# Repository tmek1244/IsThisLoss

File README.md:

# In progress
---

# Split keyboard IsThisLoss 

Welcome to the IsThisLoss repository. In this README you will find my knowledge about split keyboards, usefull materials to learn from, my steps of building this keyboard, tools I used etc. Hope that will help someone, same as mamy other usefull sources helped me.

## Table of Contents

- [Project Overview](#project-overview)
- [Usefull Recourses and Tools](#usefull-resources-and-tools)
- [Keyboard Design](#keyboard-design)
- [Tips & Tricks](#tips--tricks)

---

## Project Overview

This project is a documentation of my journey in creating a custom split keyboard. It encompasses every stage of the process, from the initial design concept to the final product. Whether you're a fellow keyboard enthusiast or just curious about the DIY keyboard-making world, this repository is meant to inspire, educate, and entertain.

## Usefull Recourses and Tools

### Youtube videos
Here are three great videos from [Ben Vallack](https://www.youtube.com/@BenVallack/videos):
- About [Ferris Sweep Compact](https://www.youtube.com/watch?v=JqpBKuEVinw&ab_channel=BenVallack) - process of ordering, customising and building that keyboard
- [Designing your custom keyboard](https://www.youtube.com/watch?v=UKfeJrRIcxw&ab_channel=BenVallack)
- [Designing your custom keyboard in depth](https://www.youtube.com/watch?v=M_VuXVErD6E&ab_channel=BenVallack)
Here is a video about KiCad, rather long tho (1:40) and its probably not necessary, but in case your would like to learn more about this powerfull tool
- [Designing STM32 PCB](https://www.youtube.com/watch?v=aVUqaB0IMh4&ab_channel=Phil%E2%80%99sLab) - KiCad tutorial

### Articles
- [FlatFootFox](https://flatfootfox.com/) - you can find there 6 articles about designing your custom keyboard with Ergogen v4. It starts from [introduction](https://flatfootfox.com/ergogen-introduction/). 
- [Kyria rev3](https://docs.splitkb.com/hc/en-us/sections/6269738440220-Aurora-Kyria-rev3-Build-Guide) - build guide, I was able to better understand building process by reading this article
- [How key matrices works](https://pcbheaven.com/wikipages/How_Key_Matrices_Works/)

### Ergopad
[Tool](https://pashutk.com/ergopad/) allowing you to try and see how your fingers moves and which layout would be the most suitable for you. Quite interesting tool, but after all I haven't used it.

### Ergogen
Open source project on [github](https://github.com/ergogen/ergogen). It provides a common configuration format to describe 2D layout and generate plates, cases and un-routed PCBs. You can clone this repo (which will be usefull at some point) or play with online version. 
There are two available versions [ergogen.xyz](https://ergogen.xyz/) and [ergogen.cache.works](https://ergogen.cache.works/), but I recommend the latter as it shows in real time how would your keyboard looks like. 

### KiCad
KiCad is a free software suite for electronic design automation. It facilitates the design and simulation of electronic hardware. It features an integrated environment for schematic capture, PCB layout, manufacturing file viewing, ngspice-provided SPICE simulation, and engineering calculation.
I found this tool pretty intuitive and if you want to just desing keyboard you really don't need to know much about this software (Ergogen will genereate most of that for you).

### ZMK
[ZMK](https://zmk.dev/) is open source keyboard firmware focused on wireless and battery-powered keyboards. Other popular option for a firmware is [QMK](https://qmk.fm/) but it doesn't support wireless keyboards. Because I wanted to have cleaner setup I went with the former.
You can find my config z[here](https://github.com/tmek1244/zmk-config).

## Keyboard Design
### Intro
I knew which layout looks the best for me - [Kyria rev3](https://splitkb.com/collections/keyboard-kits/products/kyria-rev3-pcb-kit). It has 50 keys which is a lot compared to many other split keyboards ([one key keyboard](https://www.youtube.com/watch?v=vr8LkjsRqZs&ab_channel=BenVallack)), but I didn't want to make it too compact.

### Start with Erogopad
Go checkout [Ergopad](https://pashutk.com/ergopad/), it didn't work for me, but might work for you. Having a tablet would be an advantageous as you will be tapping on screen.

### Create design in Ergogen
I had a lot of struggles with writing anything in Ergogen, until I found a tutorial about new at that time version 4 from FlatFootFox. I encourage you to go check that out. 
Important thing to metion, I only desinged one side (and probably you should too) because get the other one for free! You just put this piece on the other side. This has its consequences, namely the pins on the other side will be reversed. That means that you would have to put microcontroller on the other side too. I didn't like that much so I use footprint suggested by Ben Vallack in one of his tutorials - [promicro pretty](/ergogen/src/footprints/promicro_pretty.js). 
The config is written in yaml, if you're using [ergogen.cache.works](https://ergogen.cache.works/) you can see your progress in real time, which is realy cool. Using Ergogen you can create pcb layout (which is the main advantage), but other staff like creating cases or plates are also great.

After I though I have a good desing I generated `kicad_pcb` file (by clicking Generate on website or running `ergogen input.yaml -o output_folder` in CLI - you have pcb block in your config - [read more](https://docs.ergogen.xyz/pcbs)) and opened it in KiCad. 

Next I printed out my mockups on piece of paper, stick it to the cardboard and put switches in. This way I was able to actually feel how it's gonna be typing on this keyboard.   

### Finish PCB design

After iterating over 3 designs and choosing the best one (the standard one lol), I begin with creating actuall PCB desing. I had to switch to [CLI Ergogen](https://github.com/ergogen/ergogen) tool. I used a few new footprints, which I found in Ben Vallack [repository](https://github.com/benvallack/ergogen). In some of them I had to change a few things, as his config was written in Ergogen v3. You can find all these footprints in [/ergogen/src/footprints/](/ergogen/src/footprints/) as well as the final config [/ergogen/config.yaml](/ergogen/config.yaml). 

The final PCB looks like this:

I would really suggest to make sure that all wires are connect properly, go thorogh each connection, try to understand why it is there and so on. For me the boards costed €32.52 what in combination with the shipping time (above one week) made me really want to make sure that everything is correct. 
You can find my final PCB desing [here](/final_pcb/pcbs/keyboard.kicad_pcb) alongside with all files that Erogogen generated.

### Printing the case

When I was waiting for PCBs to arrive I bought all other necessary parts like buttons, diodes etc. You can find all parts I used in [Parts](#parts).
I also printed the case (I changed the design a little bit using Blender - one wall was to thin and I didn't want to spend more time trying to move it in Ergogen). 

### Assembly

The PCBs looks really good! I was really happy with the result.

One thing to mention, I messed up the possition of the Amongus :/ because battery wire is right above him.

When I got all the elements, I was able to finally put it toghether. 
- I started with soldering diodes (and checking every connection with multimeter).
- Then I put 3 screws per part, because I wouldn't be able to put them when switches would be soldered.
- Next I put switches in and soldered them. 
- After that I soldered microcontroller and all other elements. Nice!Nano comes without soldered pins and I didn't buy the recommended one the Mill Max as they are pretty pricey. I saw that many people use THT diodes (or other resistors) legs, but they seemed too soft for me. I found this [repo](https://github.com/joric/nrfmicro/wiki/Sockets/acb60b52e944bf0ea39e4a0f4e1fb88a0c9fdea8) where I get what I wanted. The solution was to use the male to male connectors often found in RGB led strips. Just get a good pliers.
- Last but not least I change battery connectors to JST.

After assembling the keyboards it was time to get familiar with ZMK.

### ZMK

You can check out my [current config](https://github.com/tmek1244/zmk-config). There are lots of options there, so I highly recommend to go checkout the [documentation](https://zmk.dev/). ZMK allows creating layers, which are basically different keymaps. You can switch between them using key combination. 
The most important behaviors are:
- `&kp A`- the "key press" behaviour sends standard keycodes on press/release
- `&mt LSHIFT A` - the "mod-tap" behaviour sends modifier keycode if pressed longer than 200ms, otherwise sends tap keycode
- `&mo LOWER` - the "momentary layer" behavior enables a layer while a certain key is pressed
- `&sl LOWER` - the "sticky layer" behavior enables a layer until a certain key is pressed again. I use sticky layer for activating layer with f keys.

The mod-tap behaviour is simpler version of [hold-tap](https://zmk.dev/docs/behaviors/hold-tap) which might be useful in home modifiers.

You can build firmware locally, although I spend quite some time trying to do that and I wasn't able to. I end up using [Github Actions](https://zmk.dev/docs/user-setup). You simply upload firmware to nice!nano by connecting it to your computer and double pressing reset button. Then you can just drag and drop file to the device.

## Parts
- 5x PCB (you cannot order less, but you will use two of them)
- 2x [Nice!Nano](https://nicekeyboards.com/nice-nano/)
- 48x machine sockets
- 48x machine pins
- 50x Kalih Low Profile Choc Switches (although I think that linear switches might be better - didn't tested tho)
- 48x Blank MBK Choc Low Profile Keycaps
- 2x Blank MBK Choc Low Profile Keycaps with homing bumps
- 50x SMD diodes (1N4148W)
- 2x 3.7V 110mAh LiPo battery (L401230)
- 2x ZHR-2 JST female connector (you can also solder battery directly to the board)
- 2x S2B-ZR(LF)(SN) JST male connector (also optional)
- 2x slide switches (PCM12SMTR)
- 2x buttons (B3U-1000PM)
- 12x M2x4mm screws 
- 12x threaded inserts M2x3x3.5mm for the case

## Tips & Tricks - Summary
- if you want to avoid mounting diodes you have to reduce the number of keys to number of pins available on your microcontroler (for Nice!Nano is it 17). It has to know which key was pressed and you couldn't tell it if there was a multiple keys connected to one pin right.
And that's where key matrices are used (you can read more [here](https://pcbheaven.com/wikipages/How_Key_Matrices_Works/)). It turned out being pretty easy to understand and use. Routing was a little be trickier but that's about that.
Also you may think that soldering such small parts as SMD diodes would be hard, but that's also not the case! Although you have to have a good pair of tweezers. 
- use pins from rgb led connectors

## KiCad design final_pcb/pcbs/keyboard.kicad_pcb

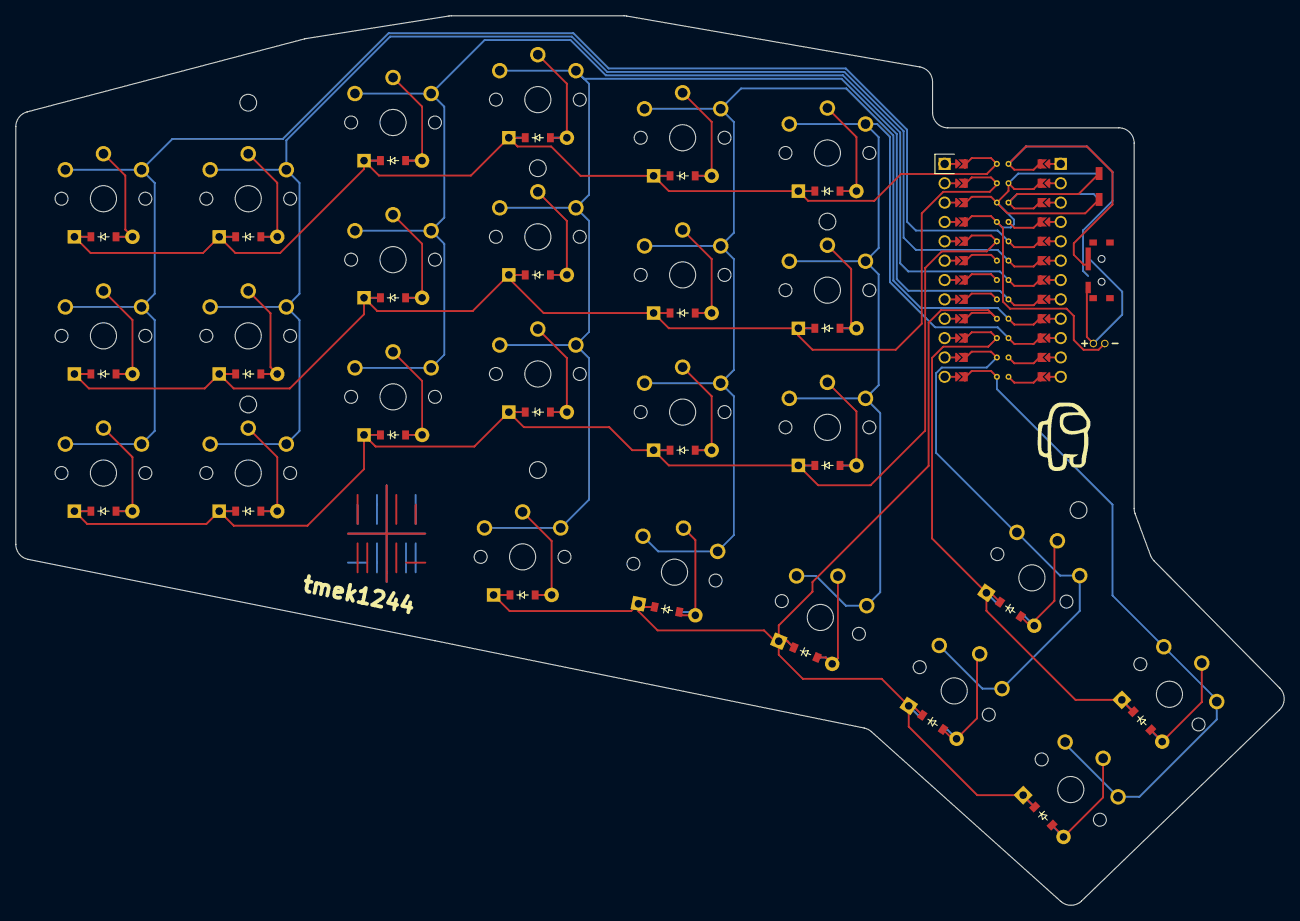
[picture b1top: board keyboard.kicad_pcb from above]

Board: 2 copper layers, 166.4 x 116.7 mm, 57 parts (0 on the bottom side), 39 nets.

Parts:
D1, D2, D3, D4, D5, D6, D7, D8, D9, D10, D11, D12, D13, D14, D15, D16, D17, D18, D19, D20, D21, D22, D23, D24, D25: ComboDiode
MCU1: ProMicro
S1, S2, S3, S4, S5, S6, S7, S8, S9, S10, S11, S12, S13, S14, S15, S16, S17, S18, S19, S20, S21, S22, S23, S24, S25: PG1350
_4, _5, _6, _7, _8, _9: MountingHole_2.2mm_M2

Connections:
GND: MCU1.2, MCU1.21, MCU1.22
P0: D2.1, D5.1, D8.1, D11.1, D14.1, D17.1, MCU1.23
P1: D3.1, D6.1, D9.1, D12.1, D15.1, D18.1, MCU1.24
P2: D1.1, D4.1, D7.1, D10.1, D13.1, D16.1, MCU1.20
P6: D19.1, D20.1, D21.1, D22.1, D24.1, MCU1.16
P7: D23.1, D25.1, MCU1.15
P8: MCU1.14, S22.1, S23.1
P9: MCU1.13, S24.1, S25.1
P14: MCU1.10, S16.1, S17.1, S18.1, S21.1
P15: MCU1.9, S13.1, S14.1, S15.1, S20.1
P18: MCU1.8, S10.1, S11.1, S12.1, S19.1
P19: MCU1.7, S7.1, S8.1, S9.1
P20: MCU1.6, S4.1, S5.1, S6.1
P21: MCU1.5, S1.1, S2.1, S3.1
index_bottom: D13.2, S13.2
index_home: D14.2, S14.2
index_top: D15.2, S15.2
inner1_lower: D19.2, S19.2
inner2_lower: D20.2, S20.2
inner_bottom: D16.2, S16.2
inner_home: D17.2, S17.2
inner_top: D18.2, S18.2
middle_bottom: D10.2, S10.2
middle_home: D11.2, S11.2
middle_lower: D21.2, S21.2
middle_top: D12.2, S12.2
outer1_lower: D22.2, S22.2
outer1_upper: D23.2, S23.2
outer2_lower: D24.2, S24.2
outer2_upper: D25.2, S25.2
outer_bottom: D1.2, S1.2
outer_home: D2.2, S2.2
outer_top: D3.2, S3.2
pinky_bottom: D4.2, S4.2
pinky_home: D5.2, S5.2
pinky_top: D6.2, S6.2
ring_bottom: D7.2, S7.2
ring_home: D8.2, S8.2
ring_top: D9.2, S9.2

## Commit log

2023-09-04 WIP: README
2023-09-05 Add next sections
2023-09-06 Add erogogen files, add a few images, update README
2023-09-09 Add photos of keyboard
2023-09-09 Update keyboard image link
2023-09-10 Add output from Ergogen, add image of kicad pcb, add list of parts
2023-09-18 Add missing parts, remove old description, finish the assembly part
2023-09-28 Create ZMK part
